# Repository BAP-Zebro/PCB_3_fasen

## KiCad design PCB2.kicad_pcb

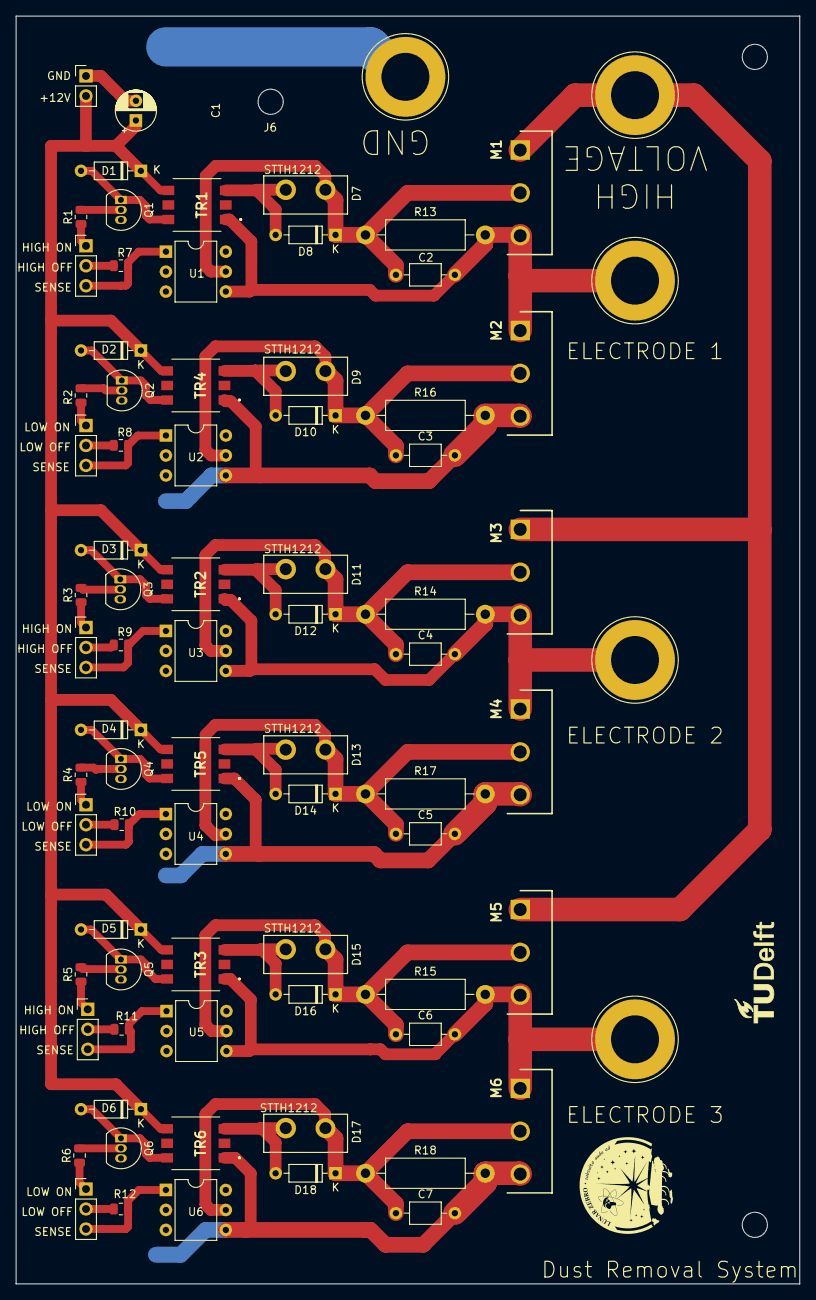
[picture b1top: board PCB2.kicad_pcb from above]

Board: 2 copper layers, 99.7 x 161.3 mm, 79 parts (0 on the bottom side), 48 nets.

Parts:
C1: 10u; CP_Radial_D5.0mm_P2.50mm
C2, C3, C4, C5, C6, C7: 100n; C_Axial_L3.8mm_D2.6mm_P7.50mm_Horizontal
D1, D2, D3, D4, D5, D6: 1N914; D_DO-35_SOD27_P7.62mm_Horizontal
D7, D9, D11, D13, D15, D17: STTH1212; STTH1212D
D8, D10, D12, D14, D16, D18: 1N4002; D_DO-35_SOD27_P7.62mm_Horizontal
J1: Conn_01x02_Male; PinHeader_1x02_P2.54mm_Vertical
JGNDh1: Conn_01x01_Male; Banana_Jack_1Pin
JH1, JH2, JH3: Conn_01x03_Male; PinHeader_1x03_P2.54mm_Vertical
JL1, JL2, JL3: Conn_01x03_Male; PinHeader_1x03_P2.54mm_Vertical
JVh1: Conn_01x01_Male; Banana_Jack_1Pin
Je1, Je2, Je3: Conn_01x01_Male; Banana_Jack_1Pin
M1, M2, M3, M4, M5, M6: STFW3N150; TO545P570X1550X3060-3P
Q1, Q2, Q3, Q4, Q5, Q6: BC547; TO-92_Inline
R1, R2, R3, R4, R5, R6: 100k; R_0805_2012Metric
R7, R8, R9, R10, R11, R12: 1k; R_0805_2012Metric
R13, R14, R15, R16, R17, R18: 10M; R_Axial_DIN0411_L9.9mm_D3.6mm_P15.24mm_Horizontal
TR1, TR2, TR3, TR4, TR5, TR6: B82804A0354A110
U1, U2, U3, U4, U5, U6: 4N35; DIP-6_W7.62mm

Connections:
+12V: C1.1, D1.1 (K), D2.1 (K), D3.1 (K), D4.1 (K), D5.1 (K), D6.1 (K), J1.2, TR1.4, TR2.4, TR3.4, TR4.4, TR5.4, TR6.4
Electrode 1: C2.2, Je1.1, M1.3 (S), M2.1 (D), R13.2, TR1.1, U1.4
Electrode 2: C4.2, Je2.1, M3.3 (S), M4.1 (D), R14.2, TR2.1, U3.4
Electrode 3: C6.2, Je3.1, M5.3 (S), M6.1 (D), R15.2, TR3.1, U5.4
GND: C1.2, C3.2, C5.2, C7.2, J1.1, JGNDh1.1, M2.3 (S), M4.3 (S), M6.3 (S), Q1.3 (E), Q2.3 (E), Q3.3 (E), Q4.3 (E), Q5.3 (E), Q6.3 (E), R16.2, R17.2, R18.2, TR4.1, TR5.1, TR6.1, U1.2, U2.2, U2.4, U3.2, U4.2, U4.4, U5.2, U6.2, U6.4
HI Side 1 Opto Monitor: JH1.3, R7.2, U1.1
HI Side 1 Turn Off: JH1.2, R7.1
HI Side 1 Turn On: JH1.1, R1.1
HI Side 2 Opto Monitor: JH2.3, R9.2, U3.1
HI Side 2 Turn Off: JH2.2, R9.1
HI Side 2 Turn On: JH2.1, R3.1
HI Side 3 Opto Monitor: JH3.3, R11.2, U5.1
HI Side 3 Turn Off: JH3.2, R11.1
HI Side 3 Turn On: JH3.1, R5.1
High Voltage Supply: JVh1.1, M1.1 (D), M3.1 (D), M5.1 (D)
LO Side 1 Opto Monitor: JL1.3, R8.2, U2.1
LO Side 1 Turn Off: JL1.2, R8.1
LO Side 1 Turn On: JL1.1, R2.1
LO Side 2 Opto Monitor: JL2.3, R10.2, U4.1
LO Side 2 Turn Off: JL2.2, R10.1
LO Side 2 Turn On: JL2.1, R4.1
LO Side 3 Opto Monitor: JL3.3, R12.2, U6.1
LO Side 3 Turn Off: JL3.2, R12.1
LO Side 3 Turn On: JL3.1, R6.1
unnamed: C2.1, D7.1 (K), D8.1 (K), M1.2 (G), R13.1, U1.5
unnamed: C3.1, D9.1 (K), D10.1 (K), M2.2 (G), R16.1, U2.5
unnamed: C4.1, D11.1 (K), D12.1 (K), M3.2 (G), R14.1, U3.5
unnamed: C5.1, D13.1 (K), D14.1 (K), M4.2 (G), R17.1, U4.5
unnamed: C6.1, D15.1 (K), D16.1 (K), M5.2 (G), R15.1, U5.5
unnamed: C7.1, D17.1 (K), D18.1 (K), M6.2 (G), R18.1, U6.5
unnamed: D1.2 (A), Q1.1 (C), TR1.6
unnamed: D2.2 (A), Q2.1 (C), TR4.6
unnamed: D3.2 (A), Q3.1 (C), TR2.6
unnamed: D4.2 (A), Q4.1 (C), TR5.6
unnamed: D5.2 (A), Q5.1 (C), TR3.6
unnamed: D6.2 (A), Q6.1 (C), TR6.6
unnamed: D7.2 (A), D8.2 (A), TR1.3
unnamed: D9.2 (A), D10.2 (A), TR4.3
unnamed: D11.2 (A), D12.2 (A), TR2.3
unnamed: D13.2 (A), D14.2 (A), TR5.3
unnamed: D15.2 (A), D16.2 (A), TR3.3
unnamed: D17.2 (A), D18.2 (A), TR6.3
unnamed: Q1.2 (B), R1.2
unnamed: Q2.2 (B), R2.2
unnamed: Q3.2 (B), R3.2
unnamed: Q4.2 (B), R4.2
unnamed: Q5.2 (B), R5.2
unnamed: Q6.2 (B), R6.2

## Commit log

2023-06-01 xoxo

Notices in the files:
parts and their libraries:
Copyright 2016 Accelerated Designs. All rights reserved.
